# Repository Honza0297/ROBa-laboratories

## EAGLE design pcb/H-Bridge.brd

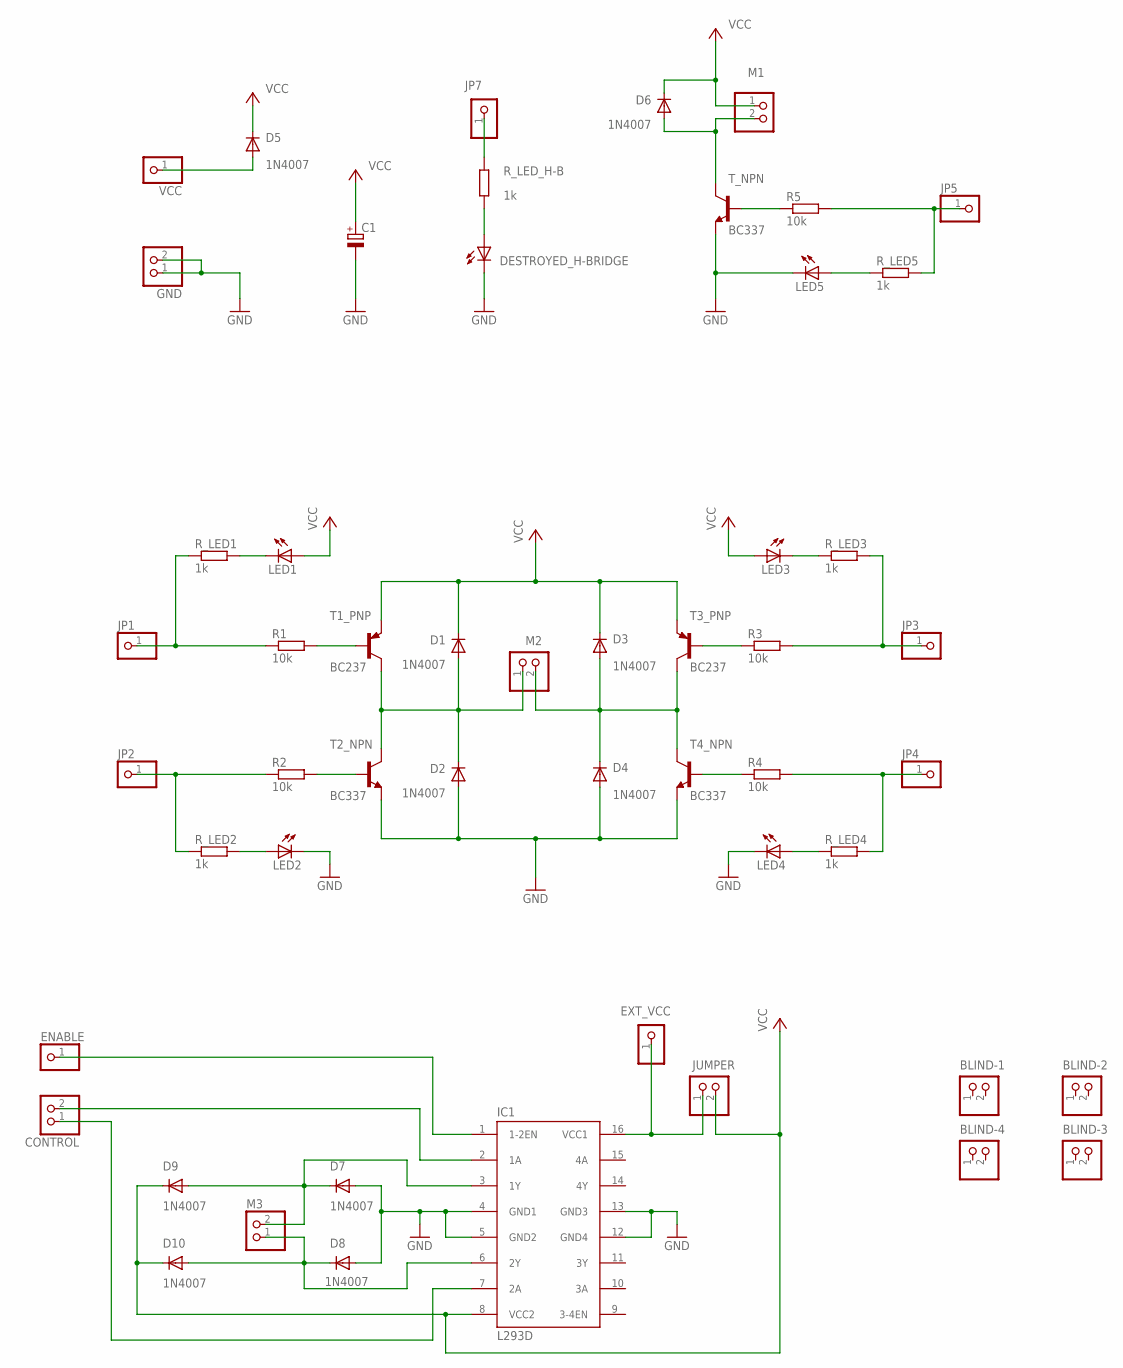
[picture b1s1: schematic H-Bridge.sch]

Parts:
BLIND-1, BLIND-2, BLIND-3, BLIND-4: PINHD-1X2; 1X02
C1: CPOL-EUE2.5-7; E2,5-7
CONTROL: PINHD-1X2; 1X02
D1, D2, D3, D4, D5, D6, D7, D8, D9, D10: 1N4007; DO41-10
DESTROYED_H-BRIDGE: LED5MM
ENABLE: PINHD-1X1; 1X01
EXT_VCC: PINHD-1X1; 1X01
GND: PINHD-1X2; 1X02
IC1: L293D; DIL16
JP1, JP2, JP3, JP4, JP5, JP7: PINHD-1X1; 1X01
JUMPER: PINHD-1X2; 1X02
LED1, LED2, LED3, LED4, LED5: LED5MM
M1, M2, M3: PINHD-1X2; 1X02
R1, R2, R3, R4, R5: 10k; 0207/12
R_LED1, R_LED2, R_LED3, R_LED4, R_LED5: 1k; 0207/12
R_LED_H-B: 1k; 0207/12
T1_PNP, T3_PNP: BC237; TO92-CBE
T2_NPN, T4_NPN: BC337; TO92-CBE
T_NPN: BC337; TO92-CBE
VCC: PINHD-1X1; 1X01

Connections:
GND: C1.-, D2.A, D4.A, D7.A, D8.A, DESTROYED_H-BRIDGE.K (C), GND.1, GND.2, IC1.4 (GND1), IC1.5 (GND2), IC1.12 (GND4), IC1.13 (GND3), LED2.K (C), LED4.K (C), LED5.K (C), T2_NPN.E, T4_NPN.E, T_NPN.E
unnamed: D1.A, D2.C, M2.1, T1_PNP.C, T2_NPN.C
unnamed: JP1.1, R1.1, R_LED1.1
unnamed: D3.A, D4.C, M2.2, T3_PNP.C, T4_NPN.C
unnamed: R1.2, T1_PNP.B
unnamed: LED1.K (C), R_LED1.2
unnamed: LED2.A, R_LED2.2
unnamed: JP2.1, R2.1, R_LED2.1
unnamed: R2.2, T2_NPN.B
unnamed: R3.1, T3_PNP.B
unnamed: LED3.K (C), R_LED3.1
unnamed: JP3.1, R3.2, R_LED3.2
unnamed: R4.1, T4_NPN.B
unnamed: JP4.1, R4.2, R_LED4.2
unnamed: D5.A, VCC.1
unnamed: LED4.A, R_LED4.1
unnamed: JP7.1, R_LED_H-B.2
unnamed: DESTROYED_H-BRIDGE.A, R_LED_H-B.1
unnamed: JP5.1, R5.2, R_LED5.2
unnamed: R5.1, T_NPN.B
unnamed: D8.C, D10.A, IC1.6 (2Y), M3.1
unnamed: LED5.A, R_LED5.1
unnamed: D6.A, M1.2, T_NPN.C
unnamed: ENABLE.1, IC1.1 (1-2EN)
unnamed: D7.C, D9.A, IC1.3 (1Y), M3.2
unnamed: EXT_VCC.1, IC1.16 (VCC1), JUMPER.1
unnamed: CONTROL.1, IC1.7 (2A)
unnamed: CONTROL.2, IC1.2 (1A)
VCC: C1.+, D1.C, D3.C, D5.C, D6.C, D9.C, D10.C, IC1.8 (VCC2), JUMPER.2, LED1.A, LED3.A, M1.1, T1_PNP.E, T3_PNP.E

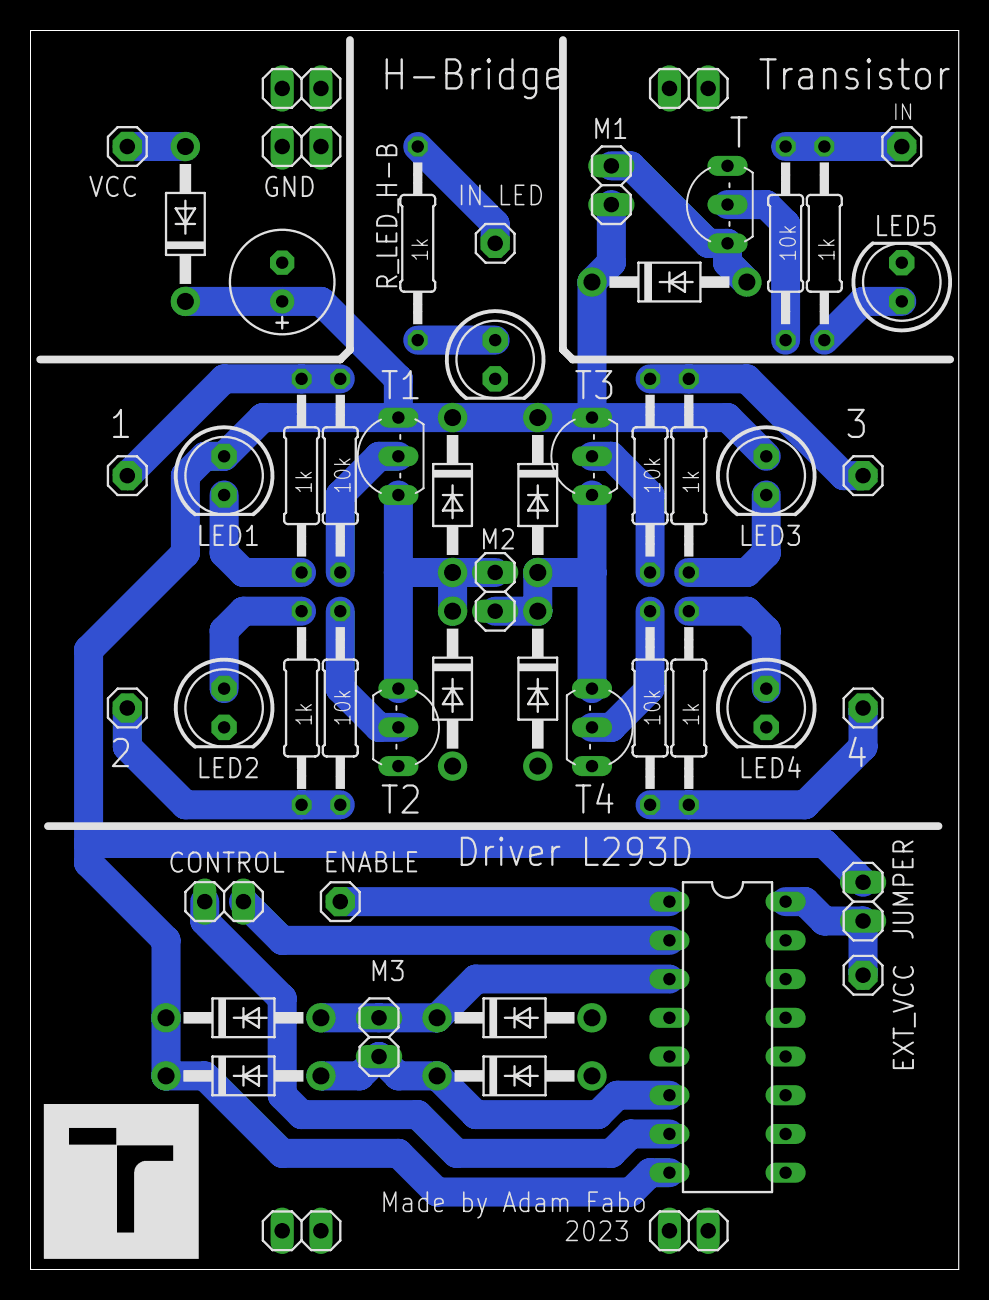
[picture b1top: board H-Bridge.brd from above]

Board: 2 copper layers, 60.9 x 81.3 mm, 53 parts (0 on the bottom side), 29 nets.

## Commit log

2022-11-07 Added sensor lab
2022-11-07 fixed typos
2023-02-06 int to double
2023-02-07 added cheat sheet
2023-02-14 typo
2023-02-14 println
2023-02-15 + L293D
2023-02-20 change
2023-03-04 Formatting folder structure
2023-03-04 + comments, formatting
2023-03-04 + Assign
2023-03-04 deleted solution
2023-03-06 changed topics
2023-03-09 + readme, fix some typos
2023-03-10 trilobot lab update
2023-03-28 + comments
2023-03-29 +new folders
2023-03-30 removed old files, comments
2023-04-03 quick fix
2023-04-06 added readme
2023-04-19 + pygame qol stuff
2023-04-24 comments, comments, comments
2023-04-26 resizable
2023-12-04 Add new version of PResentation.pdf to Trilo lab
    Including way how to operate Trilobot, connect to AP etc.
2023-12-12 trilobot_tags/ add
2024-11-13 fix: fix mistakes in sensors lab
2024-11-24 fix: fix several bugs, improve numbering
